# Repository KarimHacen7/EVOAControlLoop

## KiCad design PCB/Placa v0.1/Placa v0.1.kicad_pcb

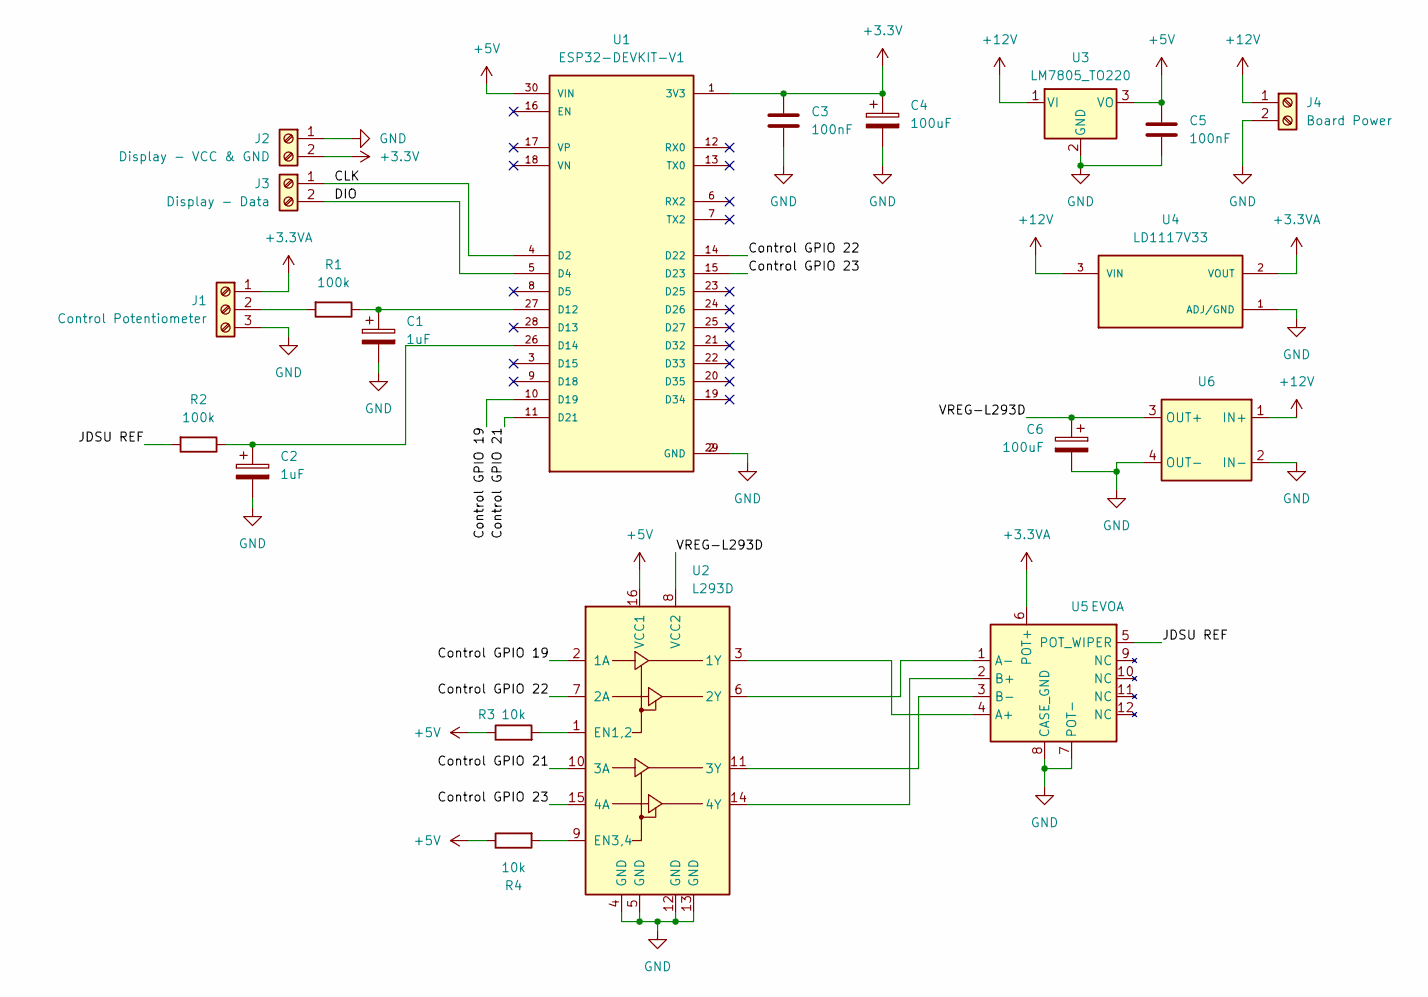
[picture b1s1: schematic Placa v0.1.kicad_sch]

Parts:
C1, C2: 1uF; CP_Radial_D8.0mm_P3.50mm_BigPad
C3, C5: 100nF; CP_Radial_D8.0mm_P3.50mm_BigPad
C4, C6: 100uF; CP_Radial_D8.0mm_P3.50mm_BigPad
J1: Control Potentiometer; TerminalBlock_bornier-3_P5.08mm
J2: Display - VCC & GND; TerminalBlock_bornier-2_P5.08mm
J3: Display - Data; TerminalBlock_bornier-2_P5.08mm
J4: Board Power; TerminalBlock_bornier-2_P5.08mm
R1, R2: 100k; R_Axial_DIN0614_L14.3mm_D5.7mm_P15.24mm_Horizontal
R3, R4: 10k; R_Axial_DIN0614_L14.3mm_D5.7mm_P15.24mm_Horizontal
U1: ESP32-DEVKIT-V1; MODULE_ESP32_DEVKIT_V1; PARTREV N/A
U2: L293D; DIP-16_W7.62mm
U3: LM7805_TO220; TO-220-3_Vertical
U4: LD1117V33; TO255P1020X450X1968-3; PARTREV 37
U5: EVOA; VCB0+1NC1.0NC1.0NC
U6: MP23070N_Module

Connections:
+3.3V: C3.1, C4.1, J2.2, U1.1 (3V3)
+3.3VA: J1.1, U4.2 (VOUT), U5.6 (POT+)
+5V: C5.1, R3.1, R4.1, U1.30 (VIN), U2.16 (VCC1), U3.3 (VO)
+12V: J4.1, U3.1 (VI), U4.3 (VIN), U6.1 (IN+)
/CLK: J3.1, U1.4 (D2)
/Control GPIO 19: U1.10 (D19), U2.2 (1A)
/Control GPIO 21: U1.11 (D21), U2.10 (3A)
/Control GPIO 22: U1.14 (D22), U2.7 (2A)
/Control GPIO 23: U1.15 (D23), U2.15 (4A)
/DIO: J3.2, U1.5 (D4)
/JDSU REF: R2.2, U5.5 (POT_WIPER)
/VREG-L293D: C6.1, U2.8 (VCC2), U6.3 (OUT+)
GND: C1.2, C2.2, C3.2, C4.2, C5.2, C6.2, J1.3, J2.1, J4.2, U1.2 (GND), U1.29 (GND), U2.4 (GND), U2.5 (GND), U2.12 (GND), U2.13 (GND), U3.2 (GND), U4.1 (ADJ/GND), U5.7 (POT-), U5.8 (CASE_GND), U6.2 (IN-), U6.4 (OUT-)
unnamed: J1.2, R1.2
unnamed: C1.1, R1.1, U1.27 (D12)
unnamed: C2.1, R2.1, U1.26 (D14)
unnamed: U2.3 (1Y), U5.4 (A+)
unnamed: U2.6 (2Y), U5.1 (A-)
unnamed: U2.11 (3Y), U5.3 (B-)
unnamed: U2.14 (4Y), U5.2 (B+)
unnamed: R3.2, U2.1 (EN1,2)
unnamed: R4.2, U2.9 (EN3,4)

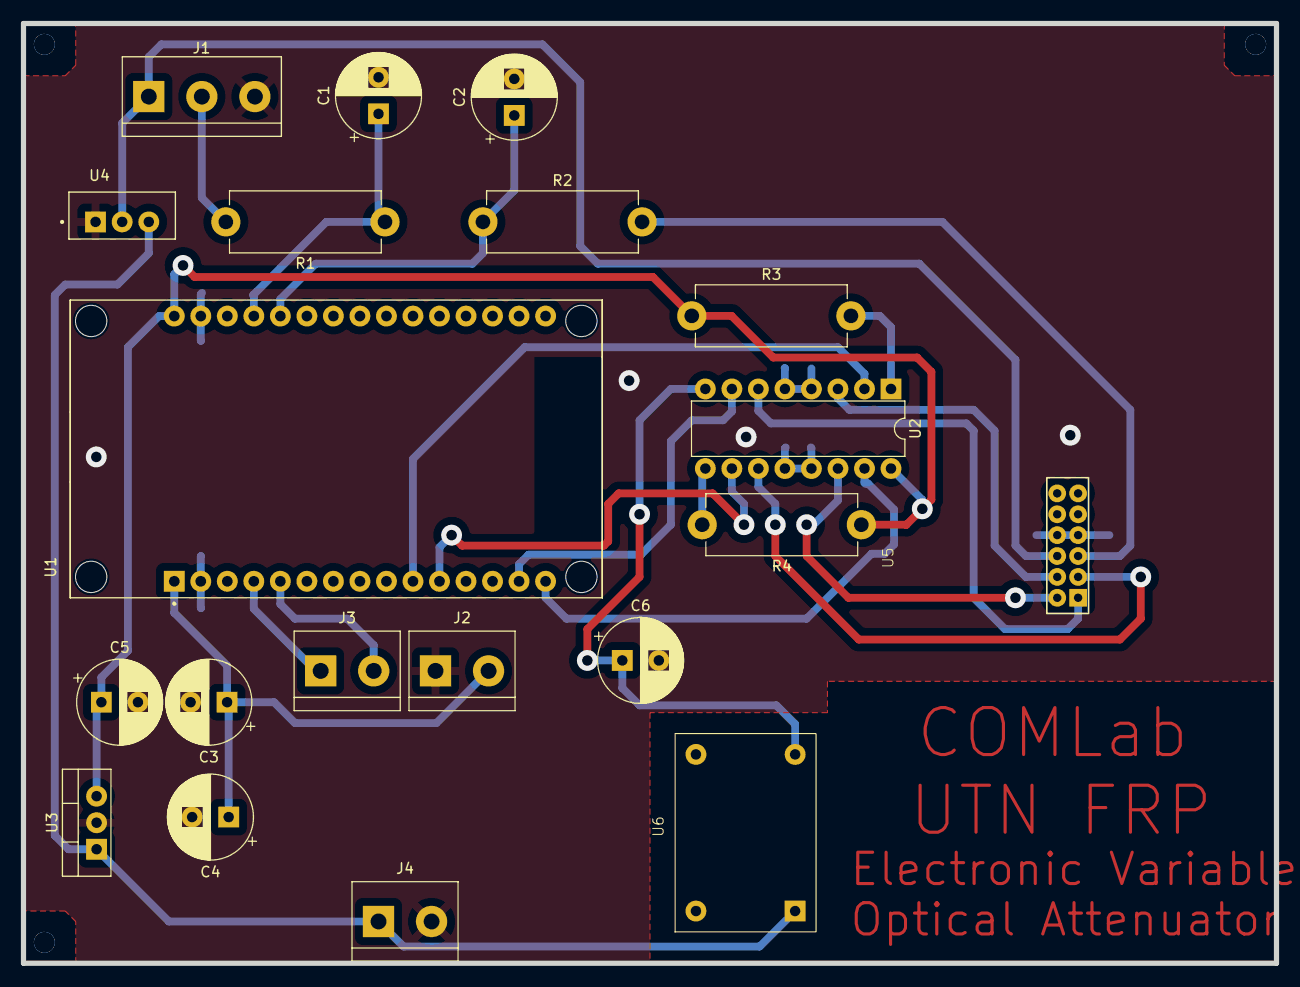
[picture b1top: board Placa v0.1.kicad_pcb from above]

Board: 2 copper layers, 120.0 x 90.0 mm, 20 parts (0 on the bottom side), 22 nets.

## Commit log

2024-07-11 Backup
